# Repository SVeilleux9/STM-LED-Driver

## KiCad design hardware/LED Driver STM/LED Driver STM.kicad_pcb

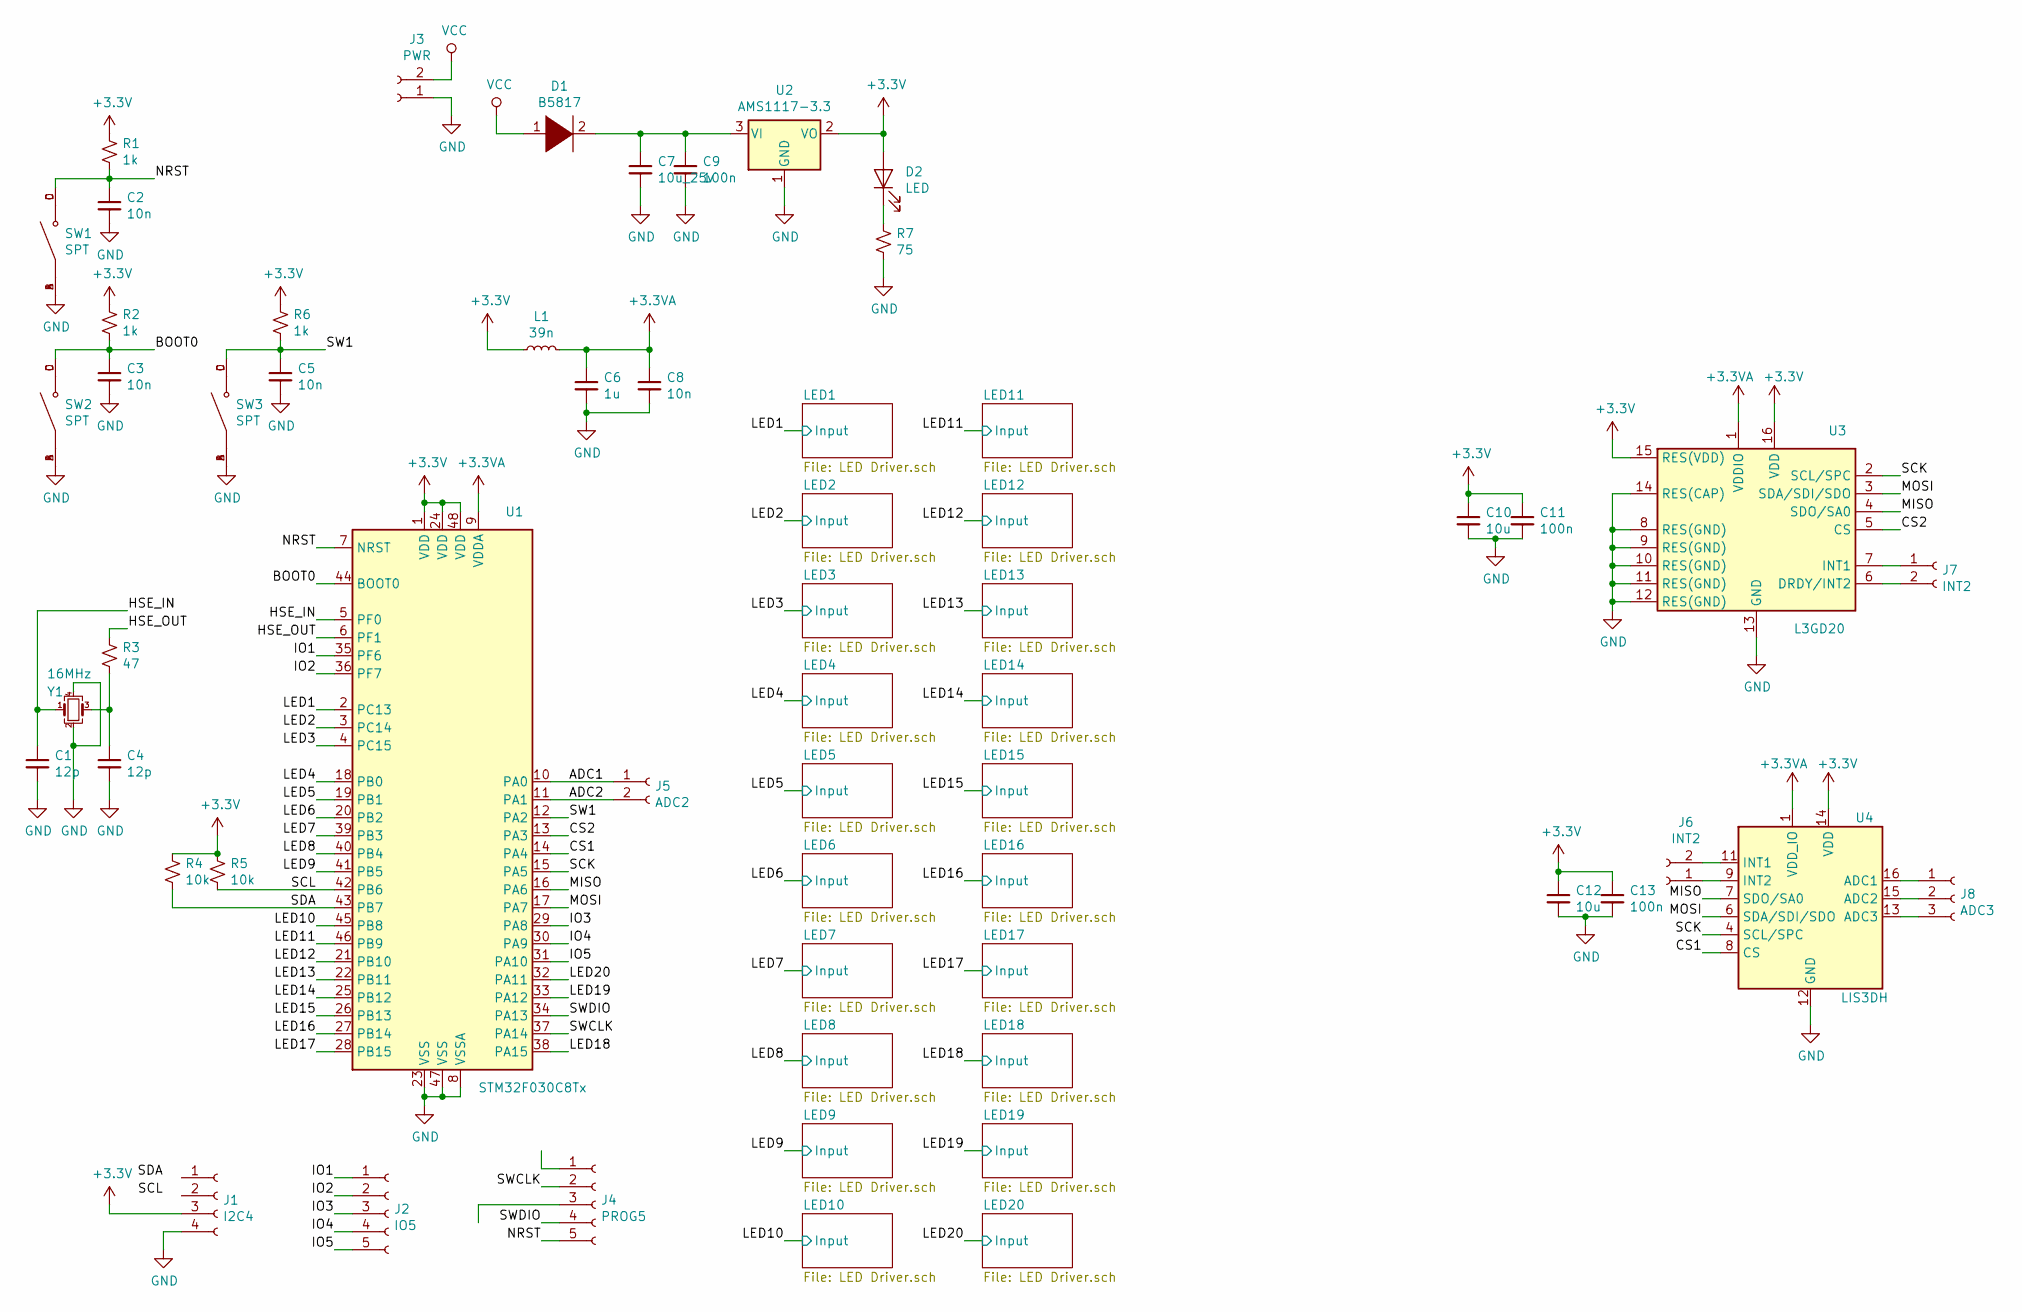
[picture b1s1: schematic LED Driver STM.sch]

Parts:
C1, C4: 12p; C_0402_1005Metric; LCSC Part # C1547
C2, C3, C5, C8: 10n; C_0402_1005Metric; LCSC Part # C15195
C6: 1u; C_0402_1005Metric; LCSC Part # C52923
C7: 10u_25v; C_0805_2012Metric; LCSC Part # C15850
C9, C11, C13: 100n; C_0402_1005Metric; LCSC Part # C1525
C10, C12: 10u; C_0402_1005Metric; LCSC Part # C15525
D1: B5817; D_SOD-123; LCSC Part # C8598
D2: LED; LED_0603_1608Metric_Castellated; LCSC Part # C2286
J1: I2C4; PinHeader_1x04_P2.54mm_Vertical
J2: IO5; PinHeader_1x05_P2.54mm_Vertical
J3: PWR; PinHeader_1x02_P2.54mm_Vertical
J4: PROG5; PinHeader_1x05_P2.54mm_Vertical
J5: ADC2; PinHeader_1x02_P2.54mm_Vertical
J6, J7: INT2; PinHeader_1x02_P2.54mm_Vertical
J8: ADC3; PinHeader_1x03_P2.54mm_Vertical
L1: 39n; L_0402_1005Metric; LCSC Part # C26443
R1, R2, R6: 1k; R_0402_1005Metric; LCSC Part # C11702
R3: 47; R_0402_1005Metric; LCSC Part # C25118
R4, R5: 10k; R_0402_1005Metric; LCSC Part # C25744
R7: 75; R_0402_1005Metric; LCSC Part # C25133
SW1, SW2, SW3: SPT; SW_TS-1187A-B-A-B; LCSC Part # C318884
U1: STM32F030C8Tx; LQFP-48_7x7mm_P0.5mm; LCSC Part # C23922
U2: AMS1117-3.3; SOT-223-3_TabPin2; LCSC Part # C6186
U3: L3GD20; LGA-16_4x4mm_P0.65mm_LayoutBorder4x4y; LCSC Part # C26444
U4: LIS3DH; LGA-16_3x3mm_P0.5mm_LayoutBorder3x5y; LCSC Part # C15134
Y1: 16MHz; Crystal_SMD_3225-4Pin_3.2x2.5mm; LCSC Part # C13738

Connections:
+3.3VA: C6.1, C8.1, L1.2, U1.9 (VDDA), U3.1 (VDDIO), U4.1 (VDD_IO)
+3V3: C10.1, C11.1, C12.1, C13.1, D2.2 (A), J1.3, L1.1, R1.1, R2.1, R4.1, R5.1, R6.1, U1.1 (VDD), U1.24 (VDD), U1.48 (VDD), U2.2 (VO), U3.15 (RES(VDD)), U3.16 (VDD), U4.14 (VDD); also elsewhere on the board
/ADC1: J5.1, U1.10 (PA0)
/ADC2: J5.2, U1.11 (PA1)
/BOOT0: C3.1, R2.2, SW2.C, SW2.D, U1.44 (BOOT0)
/CS1: U1.14 (PA4), U4.8 (CS)
/CS2: U1.13 (PA3), U3.5 (CS)
/HSE_IN: C1.1, U1.5 (PF0), Y1.1
/HSE_OUT: R3.1, U1.6 (PF1)
/IO1: J2.1, U1.35 (PF6)
/IO2: J2.2, U1.36 (PF7)
/IO3: J2.3, U1.29 (PA8)
/IO4: J2.4, U1.30 (PA9)
/IO5: J2.5, U1.31 (PA10)
/LED1: U1.2 (PC13); also elsewhere on the board
/LED2: U1.3 (PC14); also elsewhere on the board
/LED3: U1.4 (PC15); also elsewhere on the board
/LED4: U1.18 (PB0); also elsewhere on the board
/LED5: U1.19 (PB1); also elsewhere on the board
/LED6: U1.20 (PB2); also elsewhere on the board
/LED7: U1.39 (PB3); also elsewhere on the board
/LED8: U1.40 (PB4); also elsewhere on the board
/LED9: U1.41 (PB5); also elsewhere on the board
/LED10: U1.45 (PB8); also elsewhere on the board
/LED11: U1.46 (PB9); also elsewhere on the board
/LED12: U1.21 (PB10); also elsewhere on the board
/LED13: U1.22 (PB11); also elsewhere on the board
/LED14: U1.25 (PB12); also elsewhere on the board
/LED15: U1.26 (PB13); also elsewhere on the board
/LED16: U1.27 (PB14); also elsewhere on the board
/LED17: U1.28 (PB15); also elsewhere on the board
/LED18: U1.38 (PA15); also elsewhere on the board
/LED19: U1.33 (PA12); also elsewhere on the board
/LED20: U1.32 (PA11); also elsewhere on the board
/MISO: U1.16 (PA6), U3.4 (SDO/SA0), U4.7 (SDO/SA0)
/MOSI: U1.17 (PA7), U3.3 (SDA/SDI/SDO), U4.6 (SDA/SDI/SDO)
/NRST: C2.1, J4.5, R1.2, SW1.C, SW1.D, U1.7 (NRST)
/SCK: U1.15 (PA5), U3.2 (SCL/SPC), U4.4 (SCL/SPC)
/SCL: R5.2, U1.42 (PB6)
/SDA: R4.2, U1.43 (PB7)
/SW1: C5.1, R6.2, SW3.C, SW3.D, U1.12 (PA2)
/SWCLK: J4.2, U1.37 (PA14)
/SWDIO: J4.4, U1.34 (PA13)
GND: C1.2, C2.2, C3.2, C4.2, C5.2, C6.2, C7.2, C8.2, C9.2, C10.2, C11.2, C12.2, C13.2, J1.4, J3.1, R7.2, SW1.A, SW1.B, SW2.A, SW2.B, SW3.A, SW3.B, U1.8 (VSSA), U1.23 (VSS), U1.47 (VSS), U2.1 (GND), U3.8 (RES(GND)), U3.9 (RES(GND)), U3.10 (RES(GND)), U3.11 (RES(GND)), U3.12 (RES(GND)), U3.13 (GND), U3.14 (RES(CAP)), U4.5 (GND), U4.10 (GND), U4.12 (GND), Y1.2, Y1.4; also elsewhere on the board
unnamed: C4.1, R3.2, Y1.3
unnamed: C7.1, C9.1, D1.2 (A), U2.3 (VI)
unnamed: D2.1 (K), R7.1
unnamed: J6.1, U4.9 (INT2)
unnamed: J6.2, U4.11 (INT1)
unnamed: J7.1, U3.7 (INT1)
unnamed: J7.2, U3.6 (DRDY/INT2)
unnamed: J8.1, U4.16 (ADC1)
unnamed: J8.2, U4.15 (ADC2)
unnamed: J8.3, U4.13 (ADC3)
VCC: D1.1 (K), J3.2

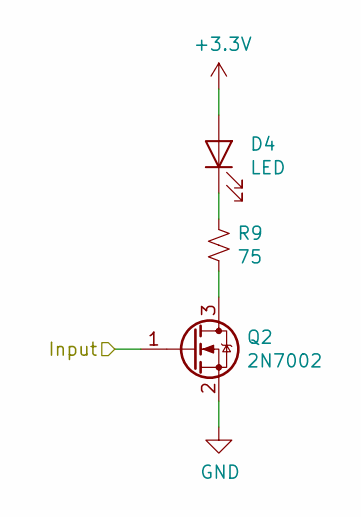
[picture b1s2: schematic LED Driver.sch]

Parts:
D4: LED; LED_0603_1608Metric_Castellated; LCSC Part # C2286
Q1: 2N7002; SOT-23; LCSC Part # C8545
R9: 75; R_0402_1005Metric; LCSC Part # C25133

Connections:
+3V3: D4.2 (A); also elsewhere on the board
/LED1: Q1.1 (G); also elsewhere on the board
GND: Q1.2 (S); also elsewhere on the board
unnamed: D4.1 (K), R9.1

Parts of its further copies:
D3, D5, D6, D7, D8, D9, D10, D11, D12, D13, D14, D15, D16, D17, D18, D19, D20, D21, D22: LED; LED_0603_1608Metric_Castellated; LCSC Part # C2286
Q2, Q3, Q4, Q5, Q6, Q7, Q8, Q9, Q10, Q11, Q12, Q13, Q14, Q15, Q16, Q17, Q18, Q19, Q20: 2N7002; SOT-23; LCSC Part # C8545
R8, R10, R11, R12, R13, R14, R15, R16, R17, R18, R19, R20, R21, R22, R23, R24, R25, R26, R27: 75; R_0402_1005Metric; LCSC Part # C25133

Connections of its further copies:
+3V3: D3.2 (A), D5.2 (A), D6.2 (A), D7.2 (A), D8.2 (A), D9.2 (A), D10.2 (A), D11.2 (A), D12.2 (A), D13.2 (A), D14.2 (A), D15.2 (A), D16.2 (A), D17.2 (A), D18.2 (A), D19.2 (A), D20.2 (A), D21.2 (A), D22.2 (A); also elsewhere on the board
/LED2: Q2.1 (G); also elsewhere on the board
/LED3: Q3.1 (G); also elsewhere on the board
/LED4: Q4.1 (G); also elsewhere on the board
/LED5: Q5.1 (G); also elsewhere on the board
/LED6: Q6.1 (G); also elsewhere on the board
/LED7: Q7.1 (G); also elsewhere on the board
/LED8: Q8.1 (G); also elsewhere on the board
/LED9: Q9.1 (G); also elsewhere on the board
/LED10: Q10.1 (G); also elsewhere on the board
/LED11: Q11.1 (G); also elsewhere on the board
/LED12: Q12.1 (G); also elsewhere on the board
/LED13: Q13.1 (G); also elsewhere on the board
/LED14: Q14.1 (G); also elsewhere on the board
/LED15: Q15.1 (G); also elsewhere on the board
/LED16: Q16.1 (G); also elsewhere on the board
/LED17: Q17.1 (G); also elsewhere on the board
/LED18: Q18.1 (G); also elsewhere on the board
/LED19: Q19.1 (G); also elsewhere on the board
/LED20: Q20.1 (G); also elsewhere on the board
GND: Q2.2 (S), Q3.2 (S), Q4.2 (S), Q5.2 (S), Q6.2 (S), Q7.2 (S), Q8.2 (S), Q9.2 (S), Q10.2 (S), Q11.2 (S), Q12.2 (S), Q13.2 (S), Q14.2 (S), Q15.2 (S), Q16.2 (S), Q17.2 (S), Q18.2 (S), Q19.2 (S), Q20.2 (S); also elsewhere on the board
unnamed: D3.1 (K), R8.1
unnamed: D5.1 (K), R10.1
unnamed: D6.1 (K), R11.1
unnamed: D7.1 (K), R12.1
unnamed: D8.1 (K), R13.1
unnamed: D9.1 (K), R14.1
unnamed: D10.1 (K), R15.1
unnamed: D11.1 (K), R16.1
unnamed: D12.1 (K), R17.1
unnamed: D13.1 (K), R18.1
unnamed: D14.1 (K), R19.1
unnamed: D15.1 (K), R20.1
unnamed: D16.1 (K), R21.1
unnamed: D17.1 (K), R22.1
unnamed: D18.1 (K), R23.1
unnamed: D19.1 (K), R24.1
unnamed: D20.1 (K), R25.1
unnamed: D21.1 (K), R26.1
unnamed: D22.1 (K), R27.1
unnamed: Q3.3 (D), R10.2
unnamed: Q4.3 (D), R11.2
unnamed: Q5.3 (D), R12.2
unnamed: Q6.3 (D), R13.2
unnamed: Q7.3 (D), R14.2
unnamed: Q8.3 (D), R15.2
unnamed: Q9.3 (D), R16.2
unnamed: Q10.3 (D), R17.2
unnamed: Q11.3 (D), R18.2
unnamed: Q12.3 (D), R19.2
unnamed: Q13.3 (D), R20.2
unnamed: Q14.3 (D), R21.2
unnamed: Q15.3 (D), R22.2
unnamed: Q16.3 (D), R23.2
unnamed: Q17.3 (D), R24.2
unnamed: Q18.3 (D), R25.2
unnamed: Q19.3 (D), R26.2
unnamed: Q20.3 (D), R27.2

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
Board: 2 copper layers, 99 parts (0 on the bottom side), 95 nets, no tracks yet.

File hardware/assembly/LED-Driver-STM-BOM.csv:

Comment,Designator,Footprint,LCSC, LCSC, LCSC Part #
"10u","C12,C10","Capacitor_SMD:C_0402_1005Metric","","C15525","C15525"
"100n","C13,C11,C9,C15,C16,C17","Capacitor_SMD:C_0402_1005Metric","","C1525","C1525"
"10n","C2,C3,C5,C8","Capacitor_SMD:C_0402_1005Metric","","C15195","C15195"
"12p","C4,C1","Capacitor_SMD:C_0402_1005Metric","","C1547","C1547"
"1u","C6","Capacitor_SMD:C_0402_1005Metric","","C52923","C52923"
"10u_25v","C7,C14","Capacitor_SMD:C_0805_2012Metric","","C15850","C15850"
"B5817","D1","Diode_SMD:D_SOD-123","","C8598","C8598"
"LED","D2,D3,D4,D5,D6,D7,D8,D9,D10,D11,D12,D13,D14,D15,D16,D17,D18,D19,D20,D21,D22","LED_SMD:LED_0603_1608Metric_Castellated","","C2286","C2286"
"I2C4","J1","Connector_PinHeader_2.54mm:PinHeader_1x04_P2.54mm_Vertical",""
"IO5","J2","Connector_PinHeader_2.54mm:PinHeader_1x05_P2.54mm_Vertical",""
"PWR","J3","Connector_PinHeader_2.54mm:PinHeader_1x02_P2.54mm_Vertical",""
"PROG5","J4","Connector_PinHeader_2.54mm:PinHeader_1x05_P2.54mm_Vertical",""
"ADC2","J5","Connector_PinHeader_2.54mm:PinHeader_1x02_P2.54mm_Vertical",""
"INT2","J7,J6","Connector_PinHeader_2.54mm:PinHeader_1x02_P2.54mm_Vertical",""
"ADC3","J8","Connector_PinHeader_2.54mm:PinHeader_1x03_P2.54mm_Vertical",""
"39n","L1","Inductor_SMD:L_0402_1005Metric","","C26443","C26443"
"2N7002","Q1,Q2,Q3,Q4,Q5,Q6,Q7,Q8,Q9,Q10,Q11,Q12,Q13,Q14,Q15,Q16,Q17,Q18,Q19,Q20","Package_TO_SOT_SMD:SOT-23","","C8545","C8545"
"1k","R1,R2,R6","Resistor_SMD:R_0402_1005Metric","","C11702","C11702"
"47","R3","Resistor_SMD:R_0402_1005Metric","","C25118","C25118"
"10k","R5,R4","Resistor_SMD:R_0402_1005Metric","","C25744","C25744"
"75","R7,R8,R9,R10,R11,R12,R13,R14,R15,R16,R17,R18,R19,R20,R21,R22,R23,R24,R25,R26,R27","Resistor_SMD:R_0402_1005Metric","","C25133","C25133"
"SPT","SW1,SW2,SW3","LCSC:SW_TS-1187A-B-A-B","","C318884","C318884"
"STM32F030C8Tx","U1","Package_QFP:LQFP-48_7x7mm_P0.5mm","","C23922","C23922"
"AMS1117-3.3","U2","Package_TO_SOT_SMD:SOT-223-3_TabPin2","","C6186","C6186"
"L3GD20","U3","Package_LGA:LGA-16_4x4mm_P0.65mm_LayoutBorder4x4y","","C26444","C26444"
"LIS3DH","U4","Package_LGA:LGA-16_3x3mm_P0.5mm_LayoutBorder3x5y","","C15134","C15134"
"16MHz","Y1","Crystal:Crystal_SMD_3225-4Pin_3.2x2.5mm","","C13738","C13738"

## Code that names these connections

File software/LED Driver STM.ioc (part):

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Mcu.Name=STM32F030C8Tx
Mcu.Package=LQFP48
Mcu.UserName=STM32F030C8Tx
PA0.Mode=IN0
PA0.Signal=ADC_IN0
PA1.Mode=IN1
PA1.Signal=ADC_IN1
PA10.Mode=Asynchronous
PA10.Signal=USART1_RX
PA11.GPIOParameters=GPIO_PuPd
PA11.GPIO_PuPd=GPIO_PULLDOWN
PA11.Signal=GPIO_Output
PA12.GPIOParameters=GPIO_PuPd
PA12.GPIO_PuPd=GPIO_PULLDOWN
PA12.Signal=GPIO_Output
PA13.Mode=Serial_Wire
PA13.Signal=SYS_SWDIO
PA14.Mode=Serial_Wire
PA14.Signal=SYS_SWCLK
PA15.GPIOParameters=GPIO_PuPd
PA15.GPIO_PuPd=GPIO_PULLDOWN
PA15.Signal=GPIO_Output
PA4.Signal=GPIO_Output
PA5.Mode=Full_Duplex_Master
PA5.Signal=SPI1_SCK
PA6.Mode=Full_Duplex_Master
PA6.Signal=SPI1_MISO
PA7.Mode=Full_Duplex_Master
PA7.Signal=SPI1_MOSI
PA9.Mode=Asynchronous
PA9.Signal=USART1_TX
PB0.GPIOParameters=GPIO_PuPd
PB0.GPIO_PuPd=GPIO_PULLDOWN
PB0.Signal=GPIO_Output
PB1.GPIOParameters=GPIO_PuPd
PB1.GPIO_PuPd=GPIO_PULLDOWN
PB1.Signal=GPIO_Output
PB10.GPIOParameters=GPIO_PuPd
PB10.GPIO_PuPd=GPIO_PULLDOWN
PB10.Signal=GPIO_Output
PB11.GPIOParameters=GPIO_PuPd
PB11.GPIO_PuPd=GPIO_PULLDOWN
PB11.Signal=GPIO_Output
PB12.GPIOParameters=GPIO_PuPd
PB12.GPIO_PuPd=GPIO_PULLDOWN
PB12.Signal=GPIO_Output
PB13.GPIOParameters=GPIO_PuPd
PB13.GPIO_PuPd=GPIO_PULLDOWN
PB13.Signal=GPIO_Output
PB14.GPIOParameters=GPIO_PuPd
PB14.GPIO_PuPd=GPIO_PULLDOWN
PB14.Signal=GPIO_Output
PB15.GPIOParameters=GPIO_PuPd
PB15.GPIO_PuPd=GPIO_PULLDOWN
PB15.Signal=GPIO_Output
PB2.GPIOParameters=GPIO_PuPd
PB2.GPIO_PuPd=GPIO_PULLDOWN
PB2.Signal=GPIO_Output
PB3.GPIOParameters=GPIO_PuPd
PB3.GPIO_PuPd=GPIO_PULLDOWN
PB3.Signal=GPIO_Output
PB4.GPIOParameters=GPIO_PuPd
PB4.GPIO_PuPd=GPIO_PULLDOWN
PB4.Signal=GPIO_Output
PB5.GPIOParameters=GPIO_PuPd
PB5.GPIO_PuPd=GPIO_PULLDOWN
PB5.Signal=GPIO_Output
PB6.Mode=I2C
PB6.Signal=I2C1_SCL
PB7.Mode=I2C
PB7.Signal=I2C1_SDA
PB8.GPIOParameters=GPIO_PuPd
PB8.GPIO_PuPd=GPIO_PULLDOWN
PB8.Signal=GPIO_Output
PB9.GPIOParameters=GPIO_PuPd
PB9.GPIO_PuPd=GPIO_PULLDOWN
PB9.Signal=GPIO_Output
PC13.GPIOParameters=GPIO_PuPd
PC13.GPIO_PuPd=GPIO_PULLDOWN
PC13.Signal=GPIO_Output
PC14-OSC32_IN.GPIOParameters=GPIO_PuPd
PC14-OSC32_IN.GPIO_PuPd=GPIO_PULLDOWN
PC14-OSC32_IN.Signal=GPIO_Output
PC15-OSC32_OUT.GPIOParameters=GPIO_PuPd
PC15-OSC32_OUT.GPIO_PuPd=GPIO_PULLDOWN
PC15-OSC32_OUT.Signal=GPIO_Output
PF0-OSC_IN.Mode=HSE-External-Oscillator
PF0-OSC_IN.Signal=RCC_OSC_IN
PF1-OSC_OUT.Mode=HSE-External-Oscillator
PF1-OSC_OUT.Signal=RCC_OSC_OUT
board=custom

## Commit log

2020-09-27 Initial Schematic Design
2020-09-27 Schematic Update
    - Added footprint for push buttons
    - Added headers for I2C pins
2020-09-27 Began Layout
    I have most of the components placed. Looks like the board will be about 65 mm diameter. Roughly 6.76 square inches (assuming 2.6x2.6 inch square.
2020-09-27 Updated layout
2020-09-27 Finished Routing V1
2020-10-04 Latest board layout
    This is the board that was purchased
2020-10-08 Create LEDnumbering.png
    Added a figure to show which LEDs align which which pins
2020-10-13 Initial code
    Its gross and doesnt work well.
2020-10-14 SPI work
    I was able to read the register who_am_i on the LIS3DH
2020-10-17 Can do a SPI read but no write
    whyyyyyyyyyyyyyy
2020-10-17 I think something is working?
    Maybe SPI is now working?
2020-10-24 Everything is working :)
    Currently the code is set to have the LED that is pointing down be turned on.
2020-10-24 Cleaned up code
    Cleaned up the code and moved mathematical equaltions to constexpr. Hid the x,y,z addresses from the accellerometer behind their own funtions so now it is accellerometer.getX() for example
2020-10-28 Starting to make v2 board
    things to do:
    - Change to 4 layer board
    - Use 4 pack of resistors 0603x4 not 0402
    - Remove fly back diodes
    - Make high current runs shorter
    - General board shrink
2020-11-03 Minor code changes
2020-11-03 added chibios
2020-11-03 remove chibios
2020-11-03 Add Chibios
2020-11-03 Create ChibiOS
2020-11-08 Latest Code
2021-01-30 Update
    Not sure when I wrote this but this is the latest code with freeRTOS and not chibiOS.
